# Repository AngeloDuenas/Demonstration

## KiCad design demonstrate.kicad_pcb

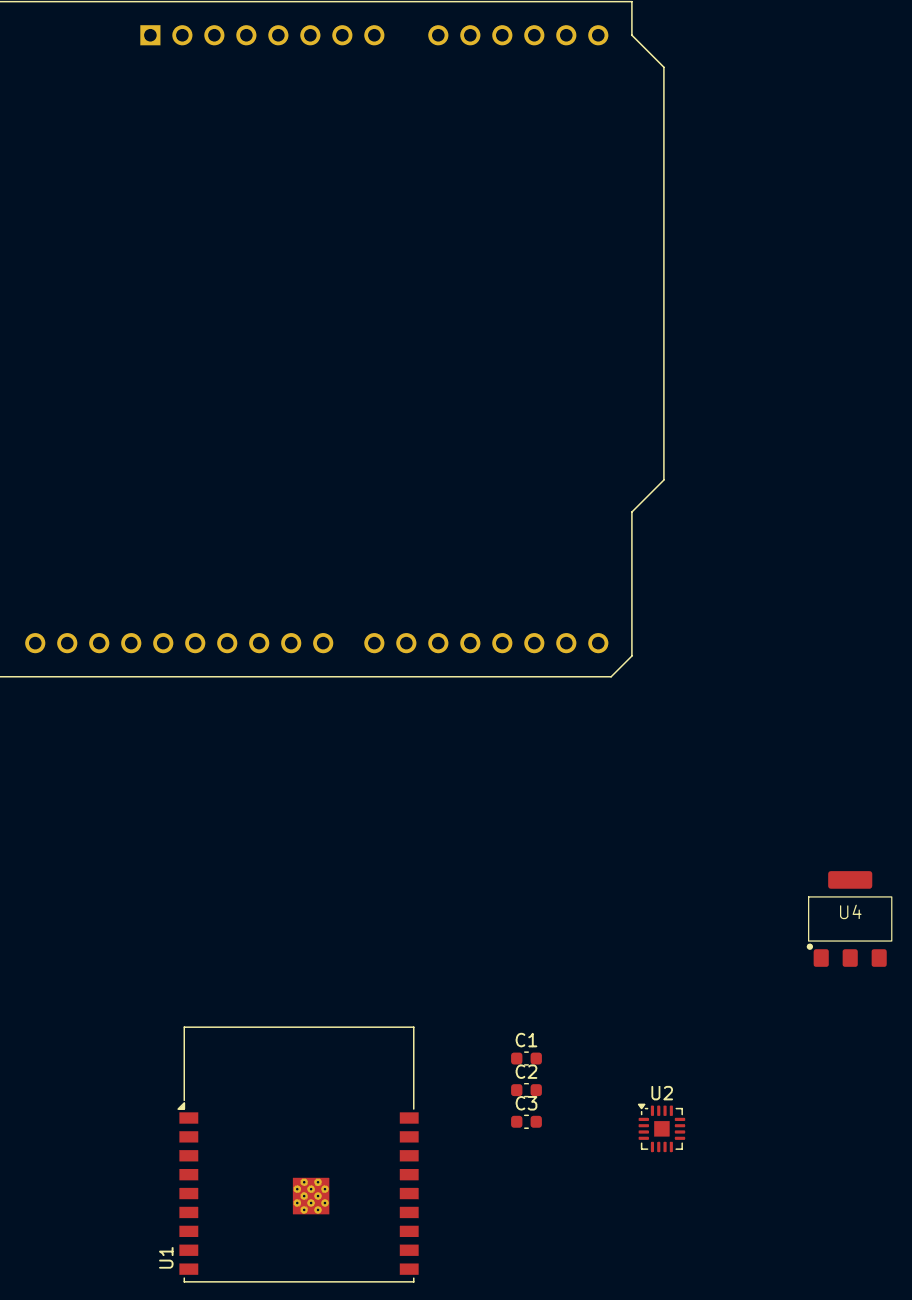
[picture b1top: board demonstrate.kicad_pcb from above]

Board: 2 copper layers, 7 parts (0 on the bottom side), 7 nets, no tracks yet.

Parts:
A1: Arduino_UNO_R3
C1: 0.1uF; C_0603_1608Metric
C2: 1uF; C_0603_1608Metric
C3: 10uF; C_0603_1608Metric
U1: ESP32-C3-WROOM-02
U2: MAX98357A; TQFN-16-1EP_3x3mm_P0.5mm_EP1.23x1.23mm
U4: AMS1117-3V3

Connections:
+3.3V: C1.1, C2.1, C3.1, U1.1 (3V3), U2.7 (VDD), U2.8 (VDD)
/BCLK: U1.16 (IO2), U2.16 (BCLK)
/DIN: U1.17 (IO1), U2.1 (DIN)
/LRCLK: U1.15 (IO3), U2.14 (LRCLK)
GND: A1.6 (GND), A1.7 (GND), A1.29 (GND), C1.2, C2.2, C3.2, U1.9 (GND), U1.19 (GND), U2.3 (GND), U2.11 (GND), U2.15 (GND), U2.17 (PAD)
unnamed: A1.16 (D1/TX), U1.12 (IO21/TXD)
unnamed: U4.1 (GND), U4.4

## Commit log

2025-06-19 First Commit
    demo
2025-06-19 Added git ignore and edited file structure
2025-06-19 Added AMS1117-3V3 footprint (YIPPPEEEE)
